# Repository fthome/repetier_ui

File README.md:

# repetier_ui

Une interface pour repetier serveur
(https://www.repetier-server.com)

*Repetier serveur est installé sur un raspberry pi.*

## Communication entrante:
Des gpio du raspberry pi (boutons) envoient du gcode aux imprimantes
- Extract filament
- Extrude 100mm à grande vitesse
- Extrude 50mm à petite vitesse
- STOP EMERGENCY
- HOME
- go to Z max

###Usage :

Modifier main.py
ex : 
'''HD = repetier_printer (repetier_api(api_key='my repetier API key'),'Nom de mon imprimante')
UI = repetier_ui(debug=False) #debug = True : pas d'envoie des gcode
UI.add_action(26,repetier_file_action("bip.gcode",HD))
UI.add_action(22,repetier_gcode_action("M18",HD))
'''
où 26 et 22 sont les GPIOxx utilisés.

Plans carte shield avec boutons : voir ./ELEC/

## Communication sortante:
Du gcode au niveau du serveur execute un script python qui pilote des prises IOT via IFTTT
- Coté Repetier-server : /var/lib/Repetier-Server/database/extcommands.xml 
- script : set_ifttt.py
- IFTTT : https://ifttt.com : If Maker Event "fan_on" then turn on Fan

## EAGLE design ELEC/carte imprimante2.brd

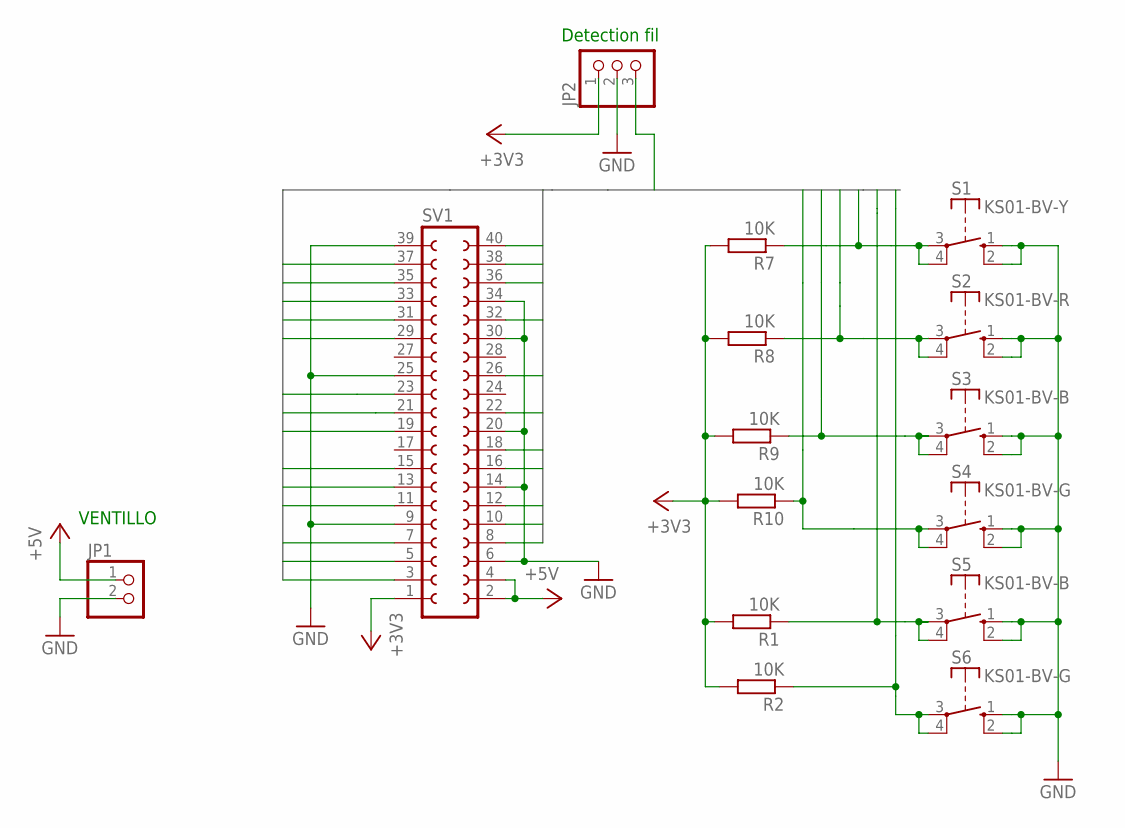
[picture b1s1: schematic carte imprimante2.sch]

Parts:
JP1: PINHD-1X02_2.54-S; 1X02-S
JP2: PINHD-1X3; 1X03
R1, R2, R7, R8, R9, R10: 10K; R0603
S1: KS01-BV-Y; DT6
S2: KS01-BV-R; DT6
S3, S5: KS01-BV-B; DT6
S4, S6: KS01-BV-G; DT6
SV1: FE20-2

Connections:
+3V3: JP2.1, R1.2, R2.2, R7.2, R8.2, R9.2, R10.2, SV1.1
+5V: JP1.1, SV1.2, SV1.4
GND: JP1.2, JP2.2, S1.1 (S), S1.2 (S), S2.1 (S), S2.2 (S), S3.1 (S), S3.2 (S), S4.1 (S), S4.2 (S), S5.1 (S), S5.2 (S), S6.1 (S), S6.2 (S), SV1.6, SV1.9, SV1.14, SV1.20, SV1.25, SV1.30, SV1.34, SV1.39
GPIO2*: SV1.3
GPIO3*: SV1.5
GPIO4: SV1.7
GPIO5: SV1.29
GPIO6: SV1.31
GPIO7*: SV1.26
GPIO9*: SV1.21
GPIO10*: R7.1, S1.3, S1.4, SV1.19
GPIO11*: SV1.23
GPIO12: SV1.32
GPIO13: SV1.33
GPIO14*: SV1.8
GPIO15*: SV1.10
GPIO16: SV1.36
GPIO17: R10.1, S4.3, S4.4, SV1.11
GPIO18: JP2.3, SV1.12
GPIO19: R1.1, S5.3, S5.4, SV1.35
GPIO20: SV1.38
GPIO21: SV1.40
GPIO22: R8.1, S2.3, S2.4, SV1.15
GPIO23: SV1.16
GPIO24: SV1.18
GPIO25: SV1.22
GPIO26: R2.1, S6.3, S6.4, SV1.37
GPIO27: R9.1, S3.3, S3.4, SV1.13

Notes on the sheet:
VENTILLO
Detection fil

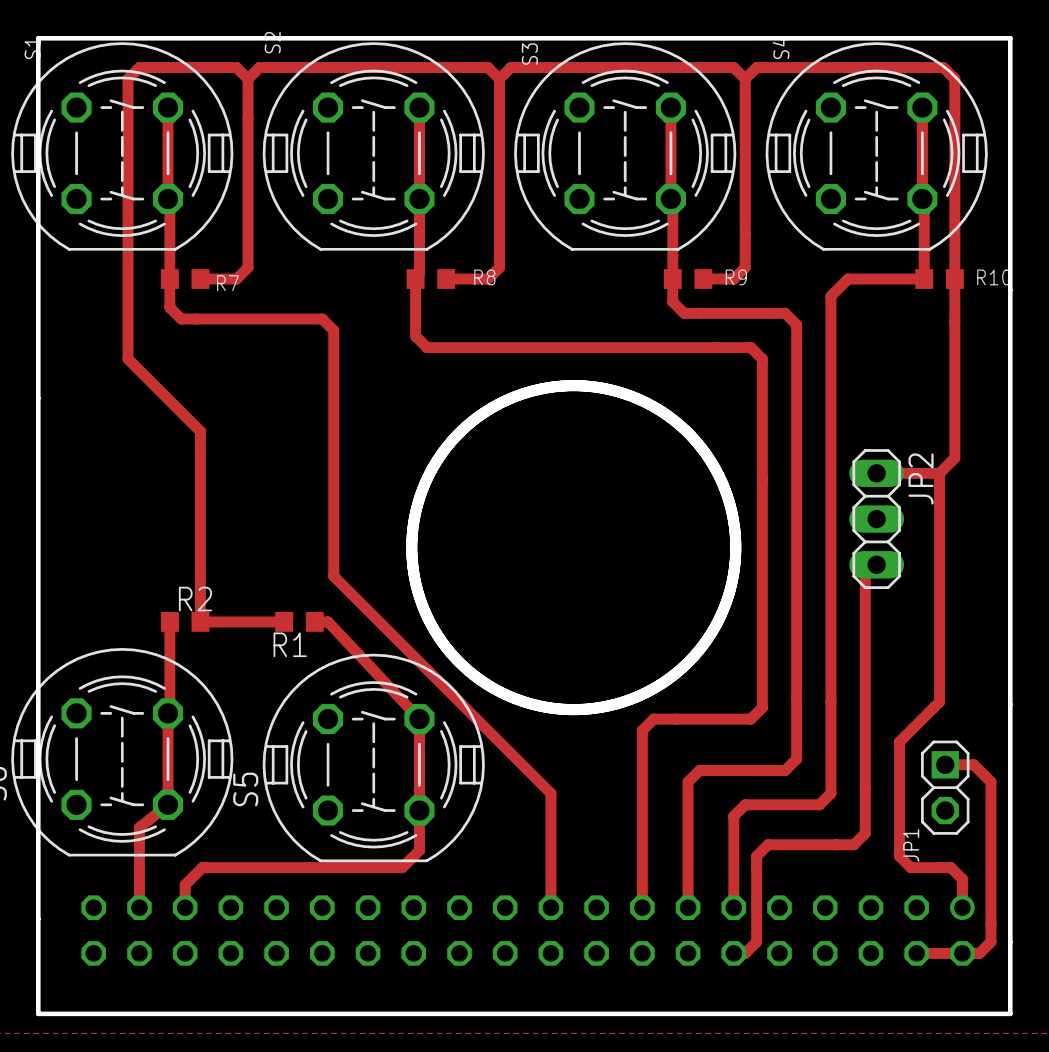
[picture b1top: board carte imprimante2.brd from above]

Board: 2 copper layers, 53.6 x 53.8 mm, 15 parts (1 on the bottom side), 10 nets.

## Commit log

2018-10-02 creation
2018-10-02 readme
2018-10-02 clean
2018-10-02 gcodes
2018-10-05 IFTTT
2018-10-10 10/10
2018-10-19 Complet
2018-10-19 action successives + action directes
2018-10-26 ifttt key outside github
2018-10-30 api vs ws
2018-11-05 Stable
2019-01-27 Wake_up
2019-01-28 filament Detection
2019-01-28 filament detection ok + successive actions ok
2019-01-28 oups
2019-03-28 only_if_has_axis
2019-03-29 bug quand imprimante éteinte
